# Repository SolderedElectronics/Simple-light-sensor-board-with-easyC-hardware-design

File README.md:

# Simple light sensor board with easyC Hardware design

## About the product

|  |
| :----------------------------------------------------------: |
|      [Buy Simple light sensor board with easyC](https://www.solde.red/333041)      |

Light is one of the most important things in the life of most living beings. This is why it is common to work with light sensors when learning about electronics. A simple light sensor has a light dependent resistor (LDR) and sensor on a breakout board for easy wiring. The simple sensor comes with easyC connectors onboard, which enables quick and easy connection with the microcontroller.

As the name suggests, an LDR will change its resistance depending on the amount of light it is exposed to. The amount of light and resistance are inversely proportional. The more light it is exposed to, the less resistance it will have. So if there is more light, the board will have a resistance of several hundred Ohms. If the resistor is in the dark, it will have a resistance of several thousand Ohms.

## Repository contents

All Soldered Electronics hardware designed in KiCAD, and repositories are organized in the following way:

- CAD folder - contains KiCAD files (Schematics, Board, Panel Board), sorted by version. Change log lists all changes between versions.
- OUTPUTS - contains useful files, such as Bill of Materials (BOM), PDF of schematics, 3D .step file of the board and gerber files, sorted by version. 
- OUTPUTS -> Compliance - Certificates and useful legal stuff. 

## Want to contribute?

Please feel free to submit a pull request if you have any contributions. We encourage you to submit an issue or pull request if you find a bug. 

## About Soldered

At Soldered, we design and manufacture a wide selection of electronic products to help you turn your ideas into acts and bring you one step closer to your final project. Our products are intented for makers and crafted in-house by our experienced team in Osijek, Croatia. We believe that sharing is a crucial element for improvement and innovation, and we work hard to stay connected with all our makers regardless of their skill or experience level. Therefore, all our products are open-source. Finally, we always have your back. If you face any problem concerning either your shopping experience or your electronics project, our team will help you deal with it, offering efficient customer service and cost-free technical support anytime. Some of those might be useful for you:

- [Web Store](https://www.soldered.com/shop)
- [Tutorials & Projects](https://soldered.com/learn)
- [Community & Technical support](https://soldered.com/community)

## License info

All Soldered open-source hardware (OSH) is under The TAPR Open Hardware License. Read more in the LICENSE file. 

No warranty - all designs in this repository are distributed in the hope that they will be useful, but without any warranty. They are provided "AS IS", therefore without warranty of any kind, either expressed or implied. The entire quality and performance of what you do with the contents of this repository are your responsibility. In no event, Soldered Electronics will be liable for your damages, losses, including any general, special, incidental or consequential damage arising out of the use or inability to use the contents of this repository. 

## Have fun! 
And thank you from your fellow makers at Soldered Electronics.

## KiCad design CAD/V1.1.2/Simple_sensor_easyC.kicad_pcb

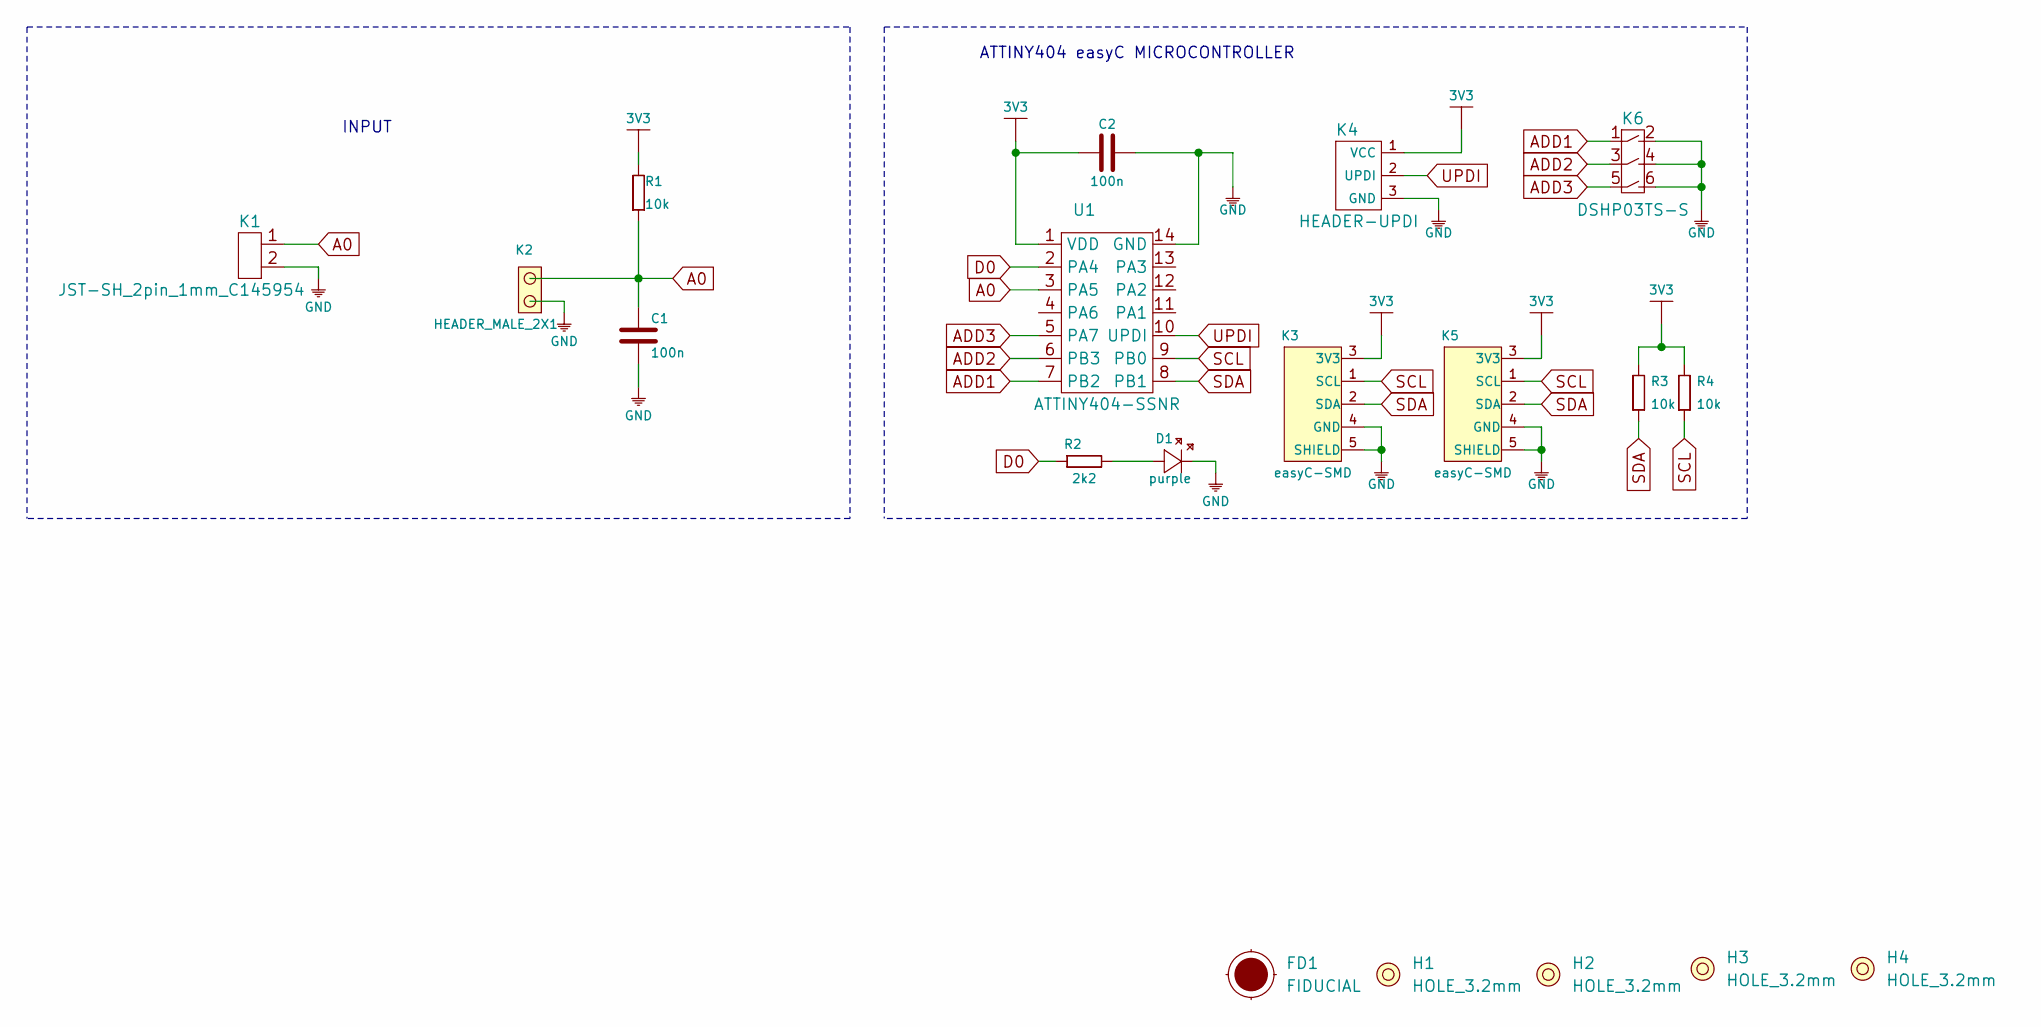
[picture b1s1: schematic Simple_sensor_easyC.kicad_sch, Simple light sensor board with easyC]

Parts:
C1, C2: 100n; 0603C
D1: purple; 0402LED
FD1: FIDUCIAL; FIDUCIAL_23
H1, H2, H3, H4: HOLE_3.2mm
K1: JST-SH_2pin_1mm_C145954
K2: HEADER_MALE_2X1
K3, K5: easyC-SMD; easyC-connector
K4: HEADER-UPDI
K6: DSHP03TS-S
R1, R3, R4: 10k; 0603R
R2: 2k2; 0402R
U1: ATTINY404-SSNR; SOIC-14

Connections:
3V3: C2.1, K3.3 (3V3), K4.1 (VCC), K5.3 (3V3), R1.2, R3.2, R4.2, U1.1 (VDD)
A0: C1.2, K1.1, K2.2, R1.1, U1.3 (PA5)
ADD1: K6.1, U1.7 (PB2)
ADD2: K6.3, U1.6 (PB3)
ADD3: K6.5, U1.5 (PA7)
D0: R2.1, U1.2 (PA4)
GND: C1.1, C2.2, D1.2 (K), K1.2, K2.1, K3.4 (GND), K3.5 (SHIELD), K4.3 (GND), K5.4 (GND), K5.5 (SHIELD), K6.2, K6.4, K6.6, U1.14 (GND)
unnamed: D1.1 (A), R2.2
SCL: K3.1 (SCL), K5.1 (SCL), R4.1, U1.9 (PB0)
SDA: K3.2 (SDA), K5.2 (SDA), R3.1, U1.8 (PB1)
UPDI: K4.2 (UPDI), U1.10 (UPDI)

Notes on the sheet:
INPUT
ATTINY404 easyC MICROCONTROLLER

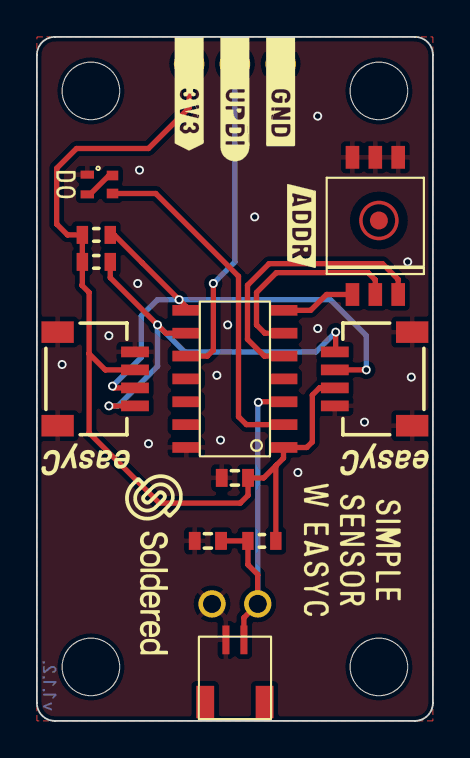
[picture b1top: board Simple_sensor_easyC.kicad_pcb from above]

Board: 2 copper layers, 22.0 x 38.0 mm, 19 parts (0 on the bottom side), 11 nets.

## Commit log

2022-08-06 Updating open source files.
